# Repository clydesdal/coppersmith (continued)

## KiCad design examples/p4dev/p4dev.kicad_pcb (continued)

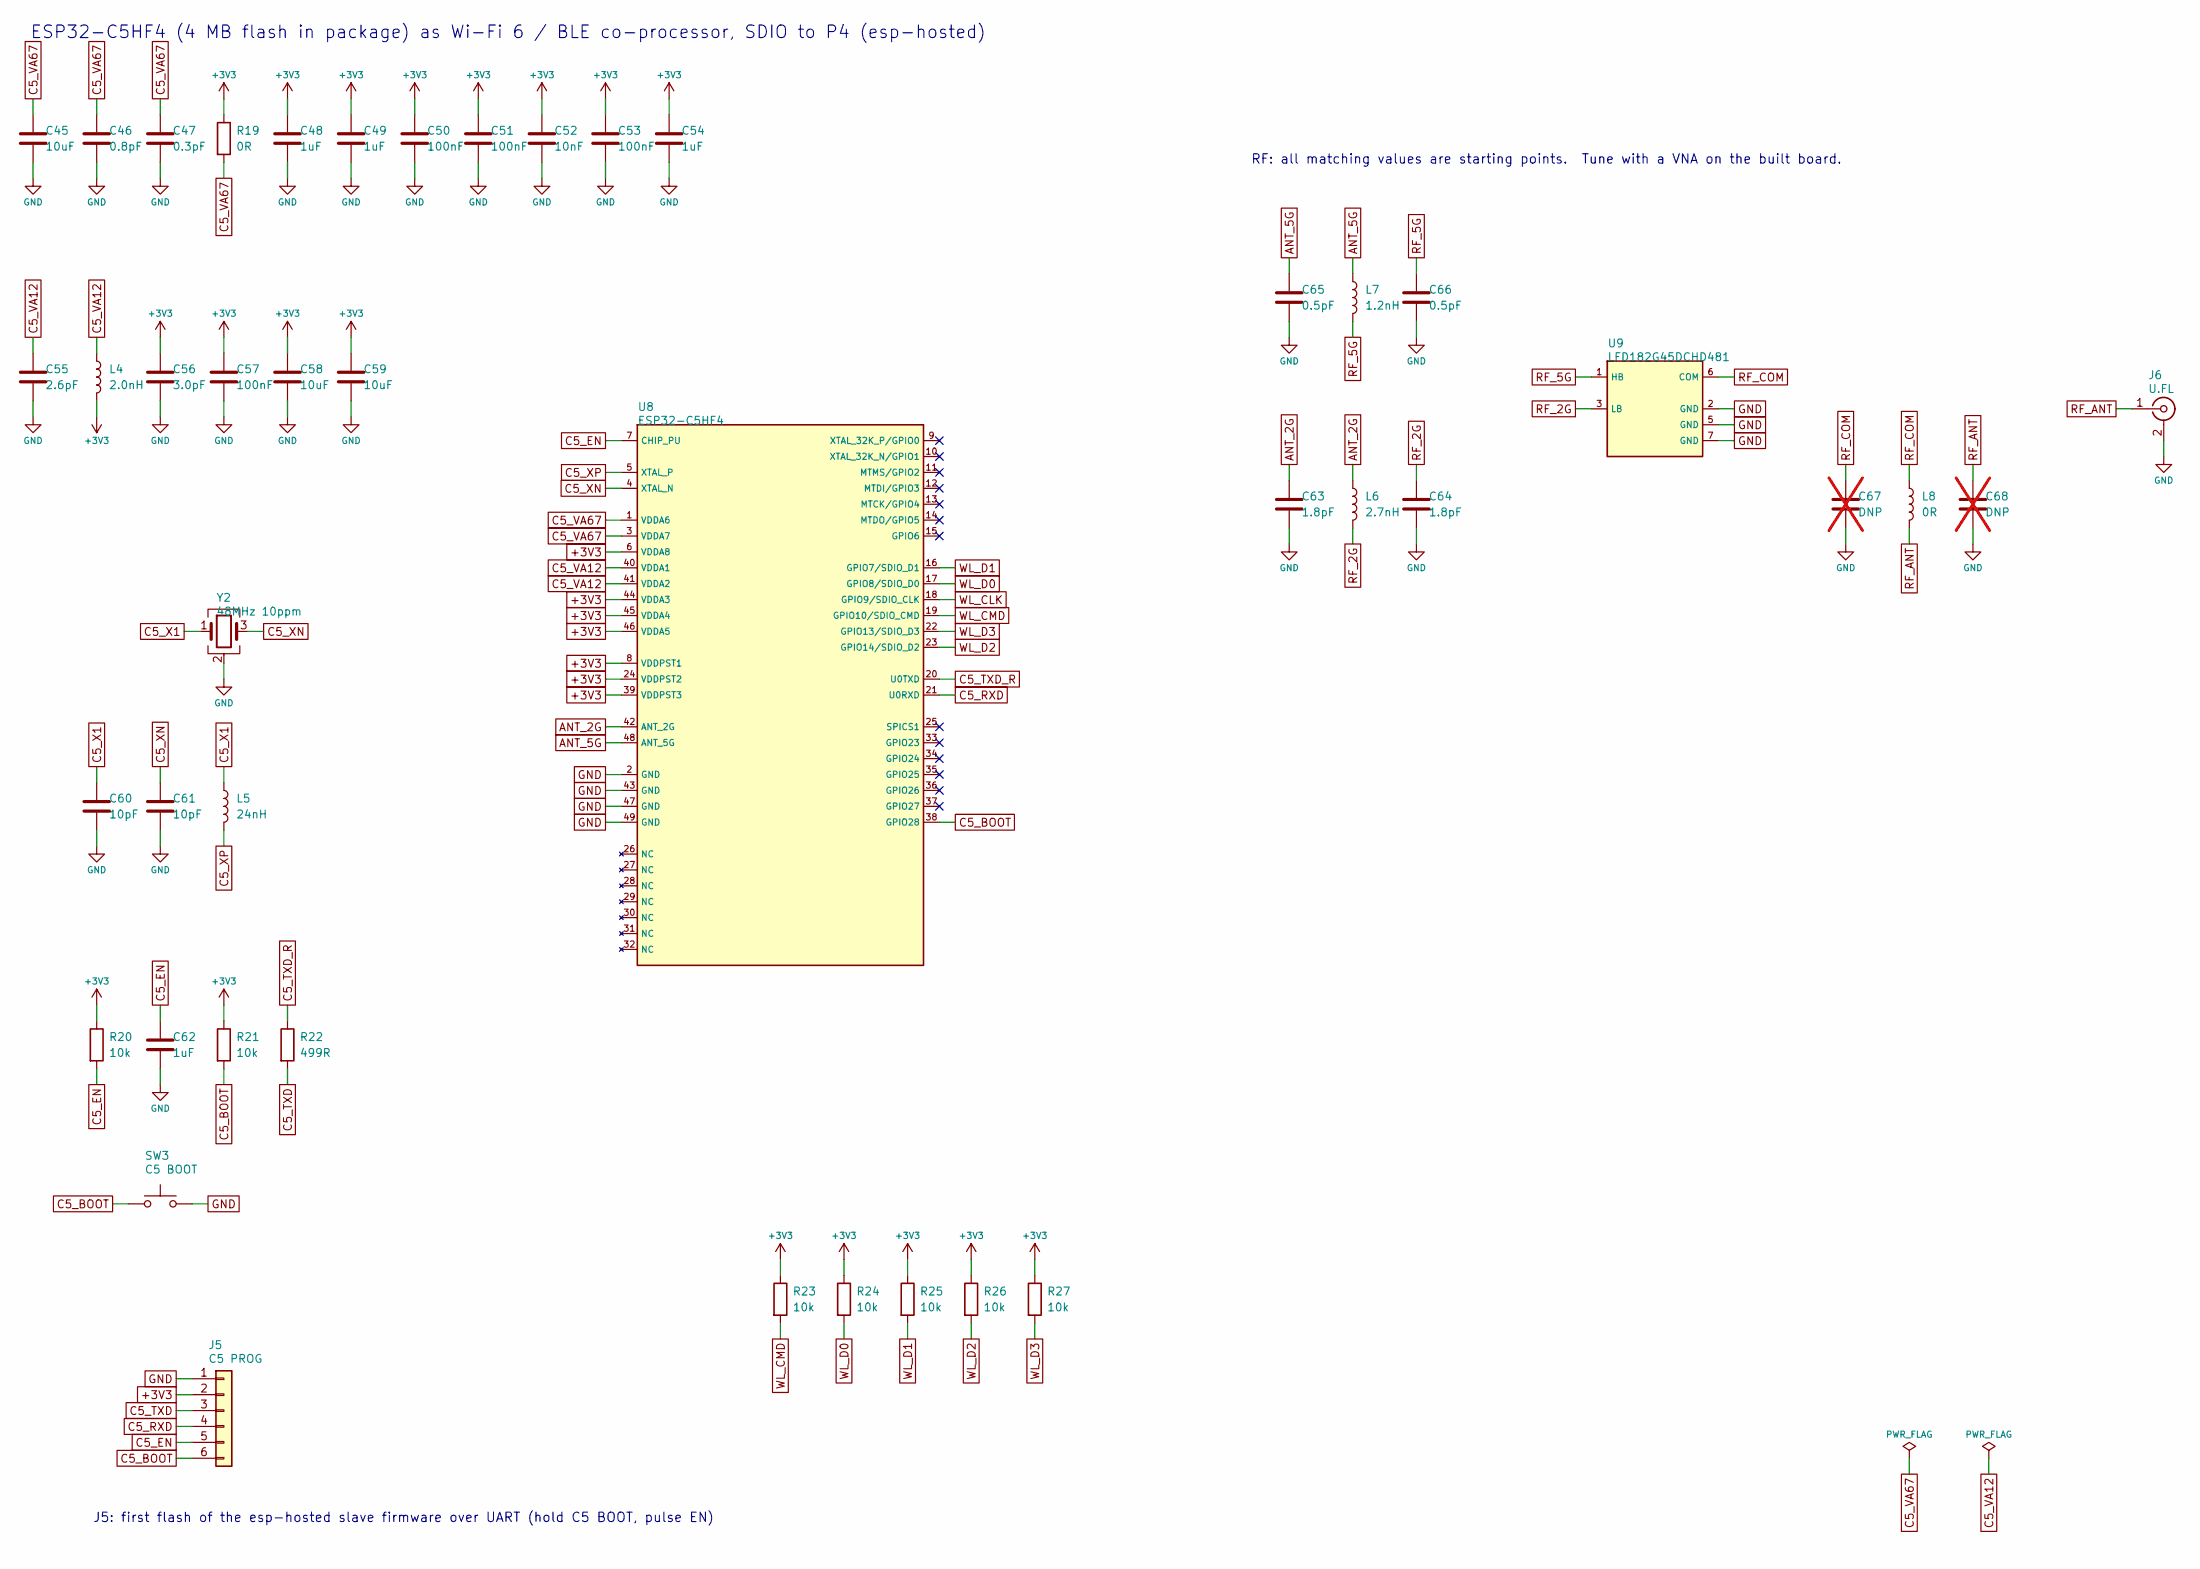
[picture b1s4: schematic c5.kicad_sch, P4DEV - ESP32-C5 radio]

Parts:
C45, C58, C59: 10uF; C_0603_1608Metric
C46: 0.8pF; C_0201_0603Metric
C47: 0.3pF; C_0201_0603Metric
C48, C49, C54, C62: 1uF; C_0402_1005Metric
C50, C51, C53, C57: 100nF; C_0402_1005Metric
C52: 10nF; C_0402_1005Metric
C55: 2.6pF; C_0201_0603Metric
C56: 3.0pF; C_0201_0603Metric
C60, C61: 10pF; C_0402_1005Metric
C63, C64: 1.8pF; C_0201_0603Metric
C65, C66: 0.5pF; C_0201_0603Metric
C67, C68: DNP; C_0201_0603Metric; not fitted
J5: C5 PROG; PinHeader_1x06_P2.54mm_Vertical; MPN Sullins PRPC006SAAN-RC
J6: U.FL; U.FL_Hirose_U.FL-R-SMT-1_Vertical; MPN Hirose U.FL-R-SMT-1(10)
L4: 2.0nH; L_0201_0603Metric
L5: 24nH; L_0402_1005Metric
L6: 2.7nH; L_0201_0603Metric
L7: 1.2nH; L_0201_0603Metric
L8: 0R; L_0201_0603Metric
R19: 0R; R_0402_1005Metric
R20, R21, R23, R24, R25, R26, R27: 10k; R_0402_1005Metric
R22: 499R; R_0402_1005Metric
SW3: C5 BOOT; SW_Push_1P1T_NO_CK_KMR2; MPN C&K KMR221GLFS
U8: ESP32-C5HF4; QFN-48-1EP_6x6mm_P0.4mm_EP4.66x4.66mm; MPN ESP32-C5HF4
U9: LFD182G45DCHD481; Murata_LFD18_Diplexer; MPN LFD182G45DCHD481
Y2: 48MHz 10ppm; Crystal_SMD_2016-4Pin_2.0x1.6mm; MPN 48 MHz, CL 8 pF, 2016

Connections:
+3V3: C48.1, C49.1, C50.1, C51.1, C52.1, C53.1, C54.1, C56.1, C57.1, C58.1, C59.1, J5.2, L4.2, R19.1, R20.1, R21.1, R23.1, R24.1, R25.1, R26.1, R27.1, U8.6 (VDDA8), U8.8 (VDDPST1), U8.24 (VDDPST2), U8.39 (VDDPST3), U8.44 (VDDA3), U8.45 (VDDA4), U8.46 (VDDA5); also elsewhere on the board
ANT_2G: C63.1, L6.1, U8.42 (ANT_2G)
ANT_5G: C65.1, L7.1, U8.48 (ANT_5G)
C5_BOOT: J5.6, R21.2, SW3.1, U8.38 (GPIO28)
C5_EN: C62.1, J5.5, R20.2, U8.7 (CHIP_PU); also elsewhere on the board
C5_RXD: J5.4, U8.21 (U0RXD)
C5_TXD: J5.3, R22.2
C5_TXD_R: R22.1, U8.20 (U0TXD)
C5_VA12: C55.1, L4.1, U8.40 (VDDA1), U8.41 (VDDA2)
C5_VA67: C45.1, C46.1, C47.1, R19.2, U8.1 (VDDA6), U8.3 (VDDA7)
C5_X1: C60.1, L5.1, Y2.1
C5_XN: C61.1, U8.4 (XTAL_N), Y2.3
C5_XP: L5.2, U8.5 (XTAL_P)
GND: C45.2, C46.2, C47.2, C48.2, C49.2, C50.2, C51.2, C52.2, C53.2, C54.2, C55.2, C56.2, C57.2, C58.2, C59.2, C60.2, C61.2, C62.2, C63.2, C64.2, C65.2, C66.2, C67.2, C68.2, J5.1, J6.2 (Ext), SW3.2, U8.2 (GND), U8.43 (GND), U8.47 (GND), U8.49 (GND), U9.2 (GND), U9.5 (GND), U9.7 (GND), Y2.2 (G), Y2.4 (G); also elsewhere on the board
RF_2G: C64.1, L6.2, U9.3 (LB)
RF_5G: C66.1, L7.2, U9.1 (HB)
RF_ANT: C68.1, J6.1 (In), L8.2
RF_COM: C67.1, L8.1, U9.6 (COM)
WL_CLK: U8.18 (GPIO9/SDIO_CLK); also elsewhere on the board
WL_CMD: R23.2, U8.19 (GPIO10/SDIO_CMD); also elsewhere on the board
WL_D0: R24.2, U8.17 (GPIO8/SDIO_D0); also elsewhere on the board
WL_D1: R25.2, U8.16 (GPIO7/SDIO_D1); also elsewhere on the board
WL_D2: R26.2, U8.23 (GPIO14/SDIO_D2); also elsewhere on the board
WL_D3: R27.2, U8.22 (GPIO13/SDIO_D3); also elsewhere on the board

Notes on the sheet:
ESP32-C5HF4 (4 MB flash in package) as Wi-Fi 6 / BLE co-processor, SDIO to P4 (esp-hosted)
RF: all matching values are starting points. Tune with a VNA on the built board.
J5: first flash of the esp-hosted slave firmware over UART (hold C5 BOOT, pulse EN)

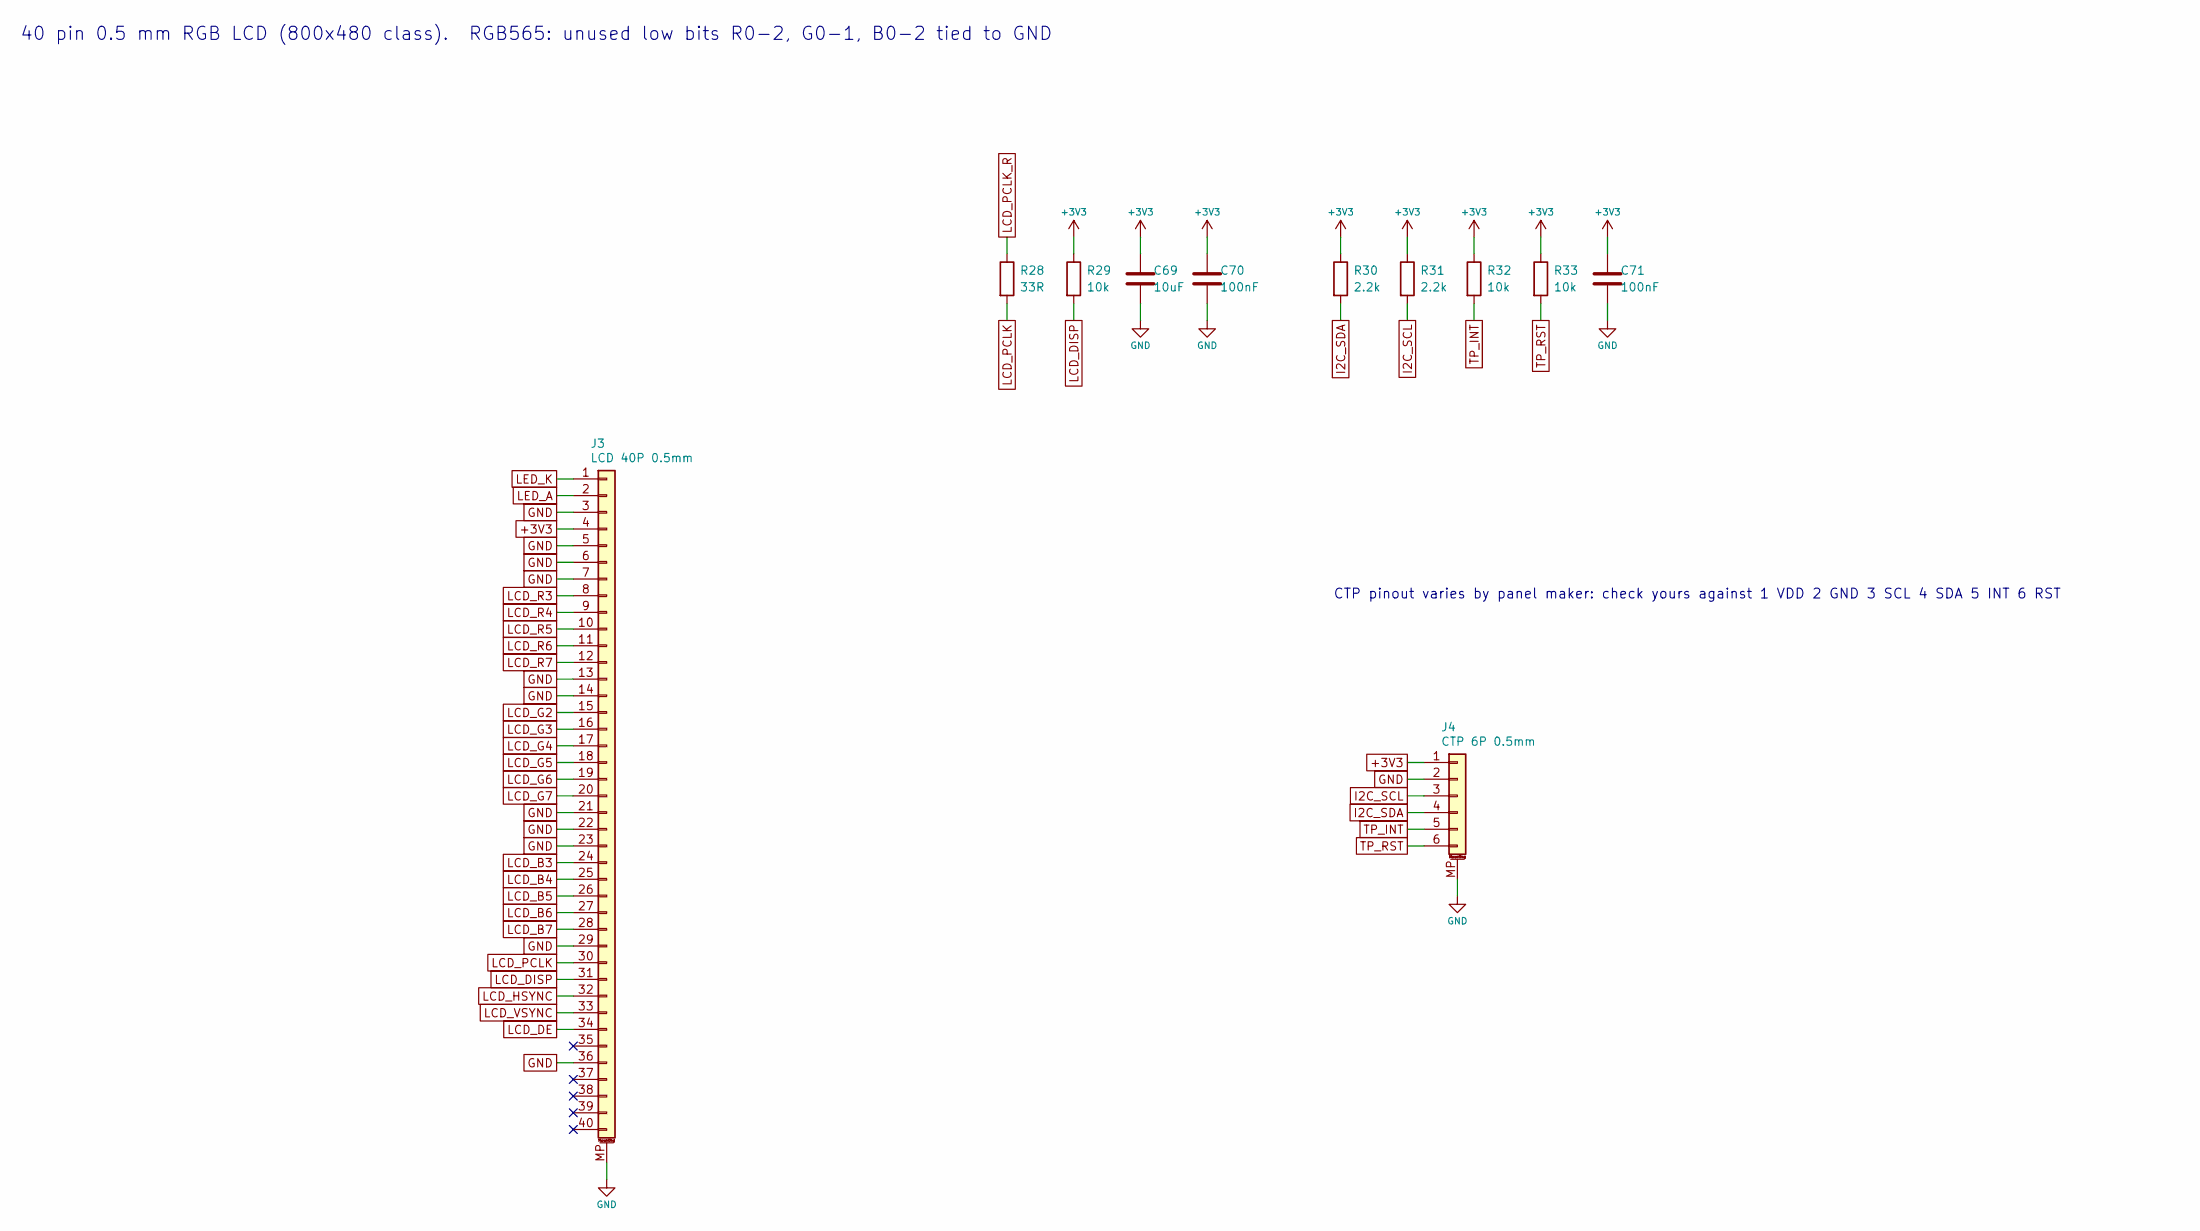
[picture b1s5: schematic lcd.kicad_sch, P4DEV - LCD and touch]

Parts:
C69: 10uF; C_0603_1608Metric
C70, C71: 100nF; C_0402_1005Metric
J3: LCD 40P 0.5mm; Hirose_FH12-40S-0.5SH_1x40-1MP_P0.50mm_Horizontal; MPN Hirose FH12-40S-0.5SH(55)
J4: CTP 6P 0.5mm; Hirose_FH12-6S-0.5SH_1x06-1MP_P0.50mm_Horizontal; MPN Hirose FH12-6S-0.5SH(55)
R28: 33R; R_0402_1005Metric
R29, R32, R33: 10k; R_0402_1005Metric
R30, R31: 2.2k; R_0402_1005Metric

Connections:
+3V3: C69.1, C70.1, C71.1, J3.4, J4.1, R29.1, R30.1, R31.1, R32.1, R33.1; also elsewhere on the board
GND: C69.2, C70.2, C71.2, J3.3, J3.5, J3.6, J3.7, J3.13, J3.14, J3.21, J3.22, J3.23, J3.29, J3.36, J3.MP (MountPin), J4.2, J4.MP (MountPin); also elsewhere on the board
I2C_SCL: J4.3, R31.2; also elsewhere on the board
I2C_SDA: J4.4, R30.2; also elsewhere on the board
LCD_B3: J3.24; also elsewhere on the board
LCD_B4: J3.25; also elsewhere on the board
LCD_B5: J3.26; also elsewhere on the board
LCD_B6: J3.27; also elsewhere on the board
LCD_B7: J3.28; also elsewhere on the board
LCD_DE: J3.34; also elsewhere on the board
LCD_DISP: J3.31, R29.2
LCD_G2: J3.15; also elsewhere on the board
LCD_G3: J3.16; also elsewhere on the board
LCD_G4: J3.17; also elsewhere on the board
LCD_G5: J3.18; also elsewhere on the board
LCD_G6: J3.19; also elsewhere on the board
LCD_G7: J3.20; also elsewhere on the board
LCD_HSYNC: J3.32; also elsewhere on the board
LCD_PCLK: J3.30, R28.2
LCD_PCLK_R: R28.1; also elsewhere on the board
LCD_R3: J3.8; also elsewhere on the board
LCD_R4: J3.9; also elsewhere on the board
LCD_R5: J3.10; also elsewhere on the board
LCD_R6: J3.11; also elsewhere on the board
LCD_R7: J3.12; also elsewhere on the board
LCD_VSYNC: J3.33; also elsewhere on the board
LED_A: J3.2; also elsewhere on the board
LED_K: J3.1; also elsewhere on the board
TP_INT: J4.5, R32.2; also elsewhere on the board
TP_RST: J4.6, R33.2; also elsewhere on the board

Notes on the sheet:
40 pin 0.5 mm RGB LCD (800x480 class). RGB565: unused low bits R0-2, G0-1, B0-2 tied to GND
CTP pinout varies by panel maker: check yours against 1 VDD 2 GND 3 SCL 4 SDA 5 INT 6 RST

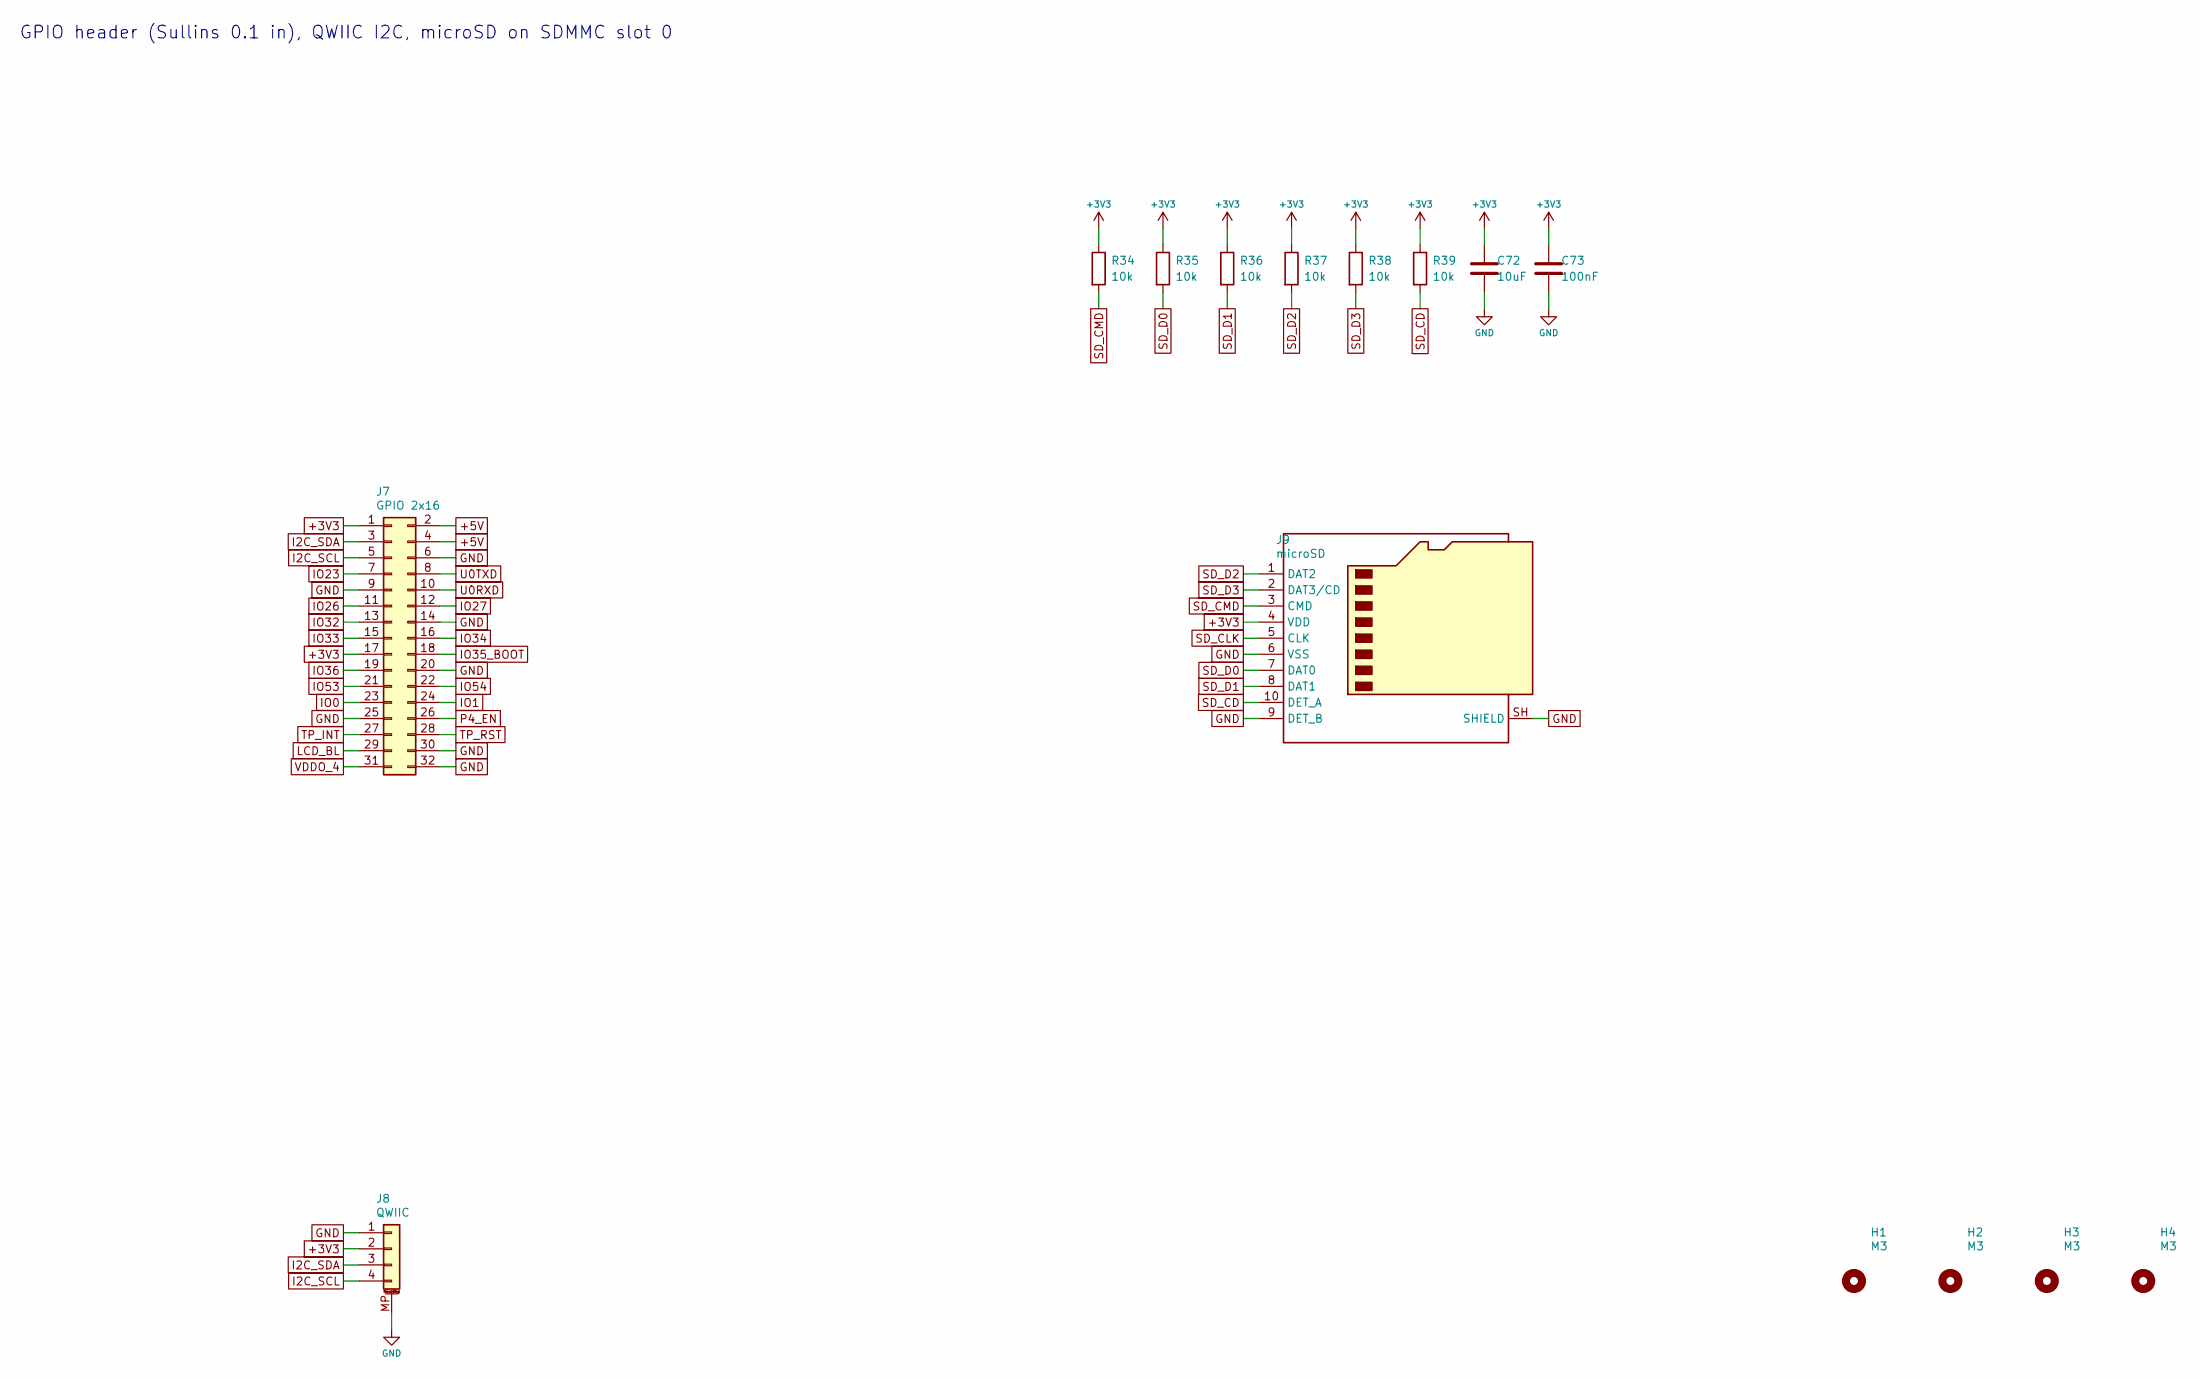
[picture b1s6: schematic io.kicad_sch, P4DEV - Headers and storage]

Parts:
C72: 10uF; C_0603_1608Metric
C73: 100nF; C_0402_1005Metric
H1, H2, H3, H4: M3; MountingHole_3.2mm_M3
J7: GPIO 2x16; PinHeader_2x16_P2.54mm_Vertical; MPN Sullins PRPC016DAAN-RC
J8: QWIIC; JST_SH_SM04B-SRSS-TB_1x04-1MP_P1.00mm_Horizontal; MPN JST SM04B-SRSS-TB
J9: microSD; microSD_HC_Hirose_DM3AT-SF-PEJM5; MPN Hirose DM3AT-SF-PEJM5
R34, R35, R36, R37, R38, R39: 10k; R_0402_1005Metric

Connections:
+3V3: C72.1, C73.1, J7.1, J7.17, J8.2, J9.4 (VDD), R34.1, R35.1, R36.1, R37.1, R38.1, R39.1; also elsewhere on the board
+5V: J7.2, J7.4; also elsewhere on the board
GND: C72.2, C73.2, J7.6, J7.9, J7.14, J7.20, J7.25, J7.30, J7.32, J8.1, J8.MP (MountPin), J9.6 (VSS), J9.9 (DET_B), J9.SH (SHIELD); also elsewhere on the board
I2C_SCL: J7.5, J8.4; also elsewhere on the board
I2C_SDA: J7.3, J8.3; also elsewhere on the board
IO0: J7.23; also elsewhere on the board
IO1: J7.24; also elsewhere on the board
IO23: J7.7; also elsewhere on the board
IO26: J7.11; also elsewhere on the board
IO27: J7.12; also elsewhere on the board
IO32: J7.13; also elsewhere on the board
IO33: J7.15; also elsewhere on the board
IO34: J7.16; also elsewhere on the board
IO35_BOOT: J7.18; also elsewhere on the board
IO36: J7.19; also elsewhere on the board
IO53: J7.21; also elsewhere on the board
IO54: J7.22; also elsewhere on the board
LCD_BL: J7.29; also elsewhere on the board
P4_EN: J7.26; also elsewhere on the board
SD_CD: J9.10 (DET_A), R39.2; also elsewhere on the board
SD_CLK: J9.5 (CLK); also elsewhere on the board
SD_CMD: J9.3 (CMD), R34.2; also elsewhere on the board
SD_D0: J9.7 (DAT0), R35.2; also elsewhere on the board
SD_D1: J9.8 (DAT1), R36.2; also elsewhere on the board
SD_D2: J9.1 (DAT2), R37.2; also elsewhere on the board
SD_D3: J9.2 (DAT3/CD), R38.2; also elsewhere on the board
TP_INT: J7.27; also elsewhere on the board
TP_RST: J7.28; also elsewhere on the board
U0RXD: J7.10; also elsewhere on the board
U0TXD: J7.8; also elsewhere on the board
VDDO_4: J7.31; also elsewhere on the board

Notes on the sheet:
GPIO header (Sullins 0.1 in), QWIIC I2C, microSD on SDMMC slot 0

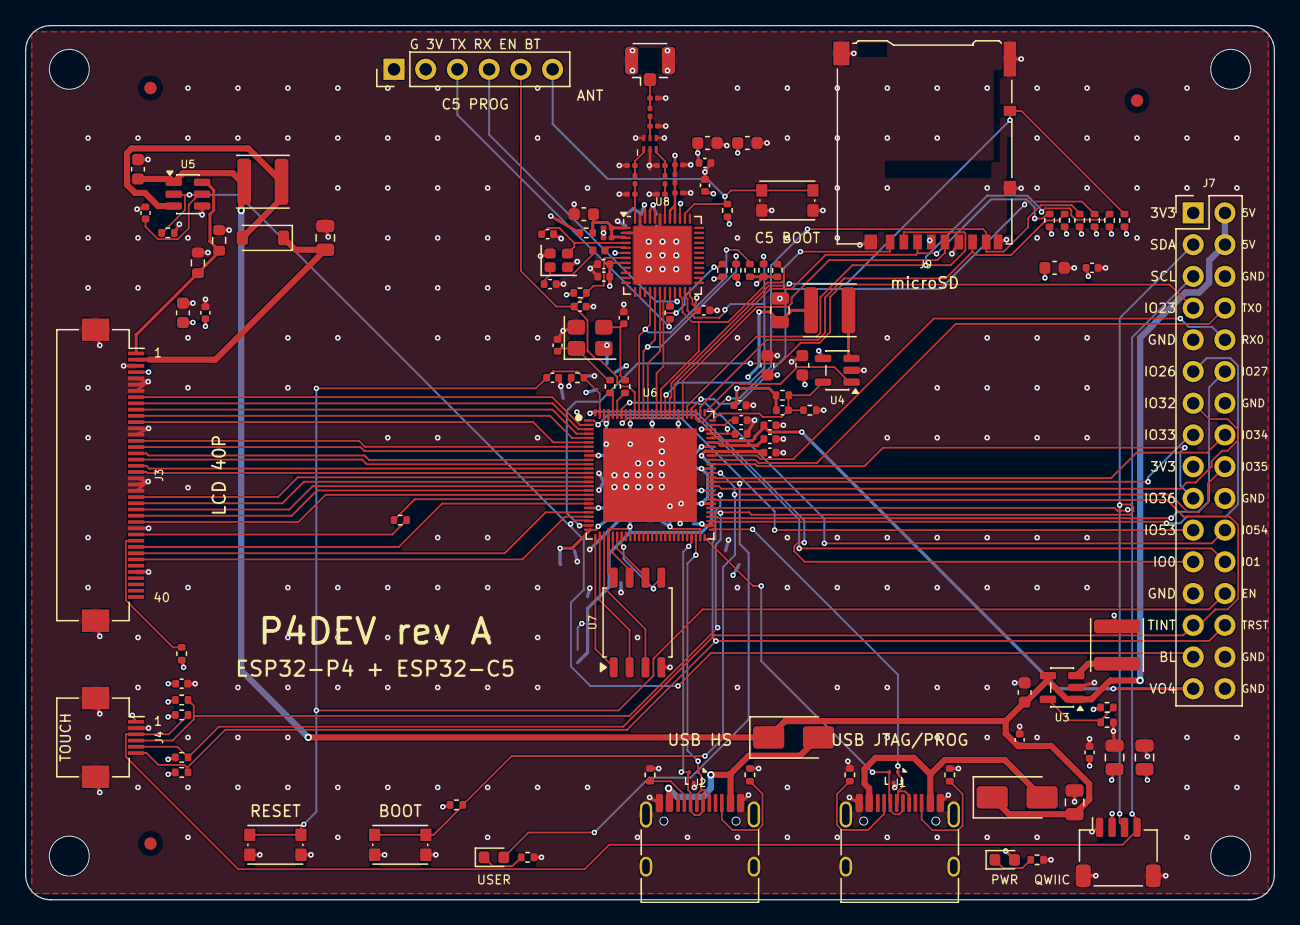
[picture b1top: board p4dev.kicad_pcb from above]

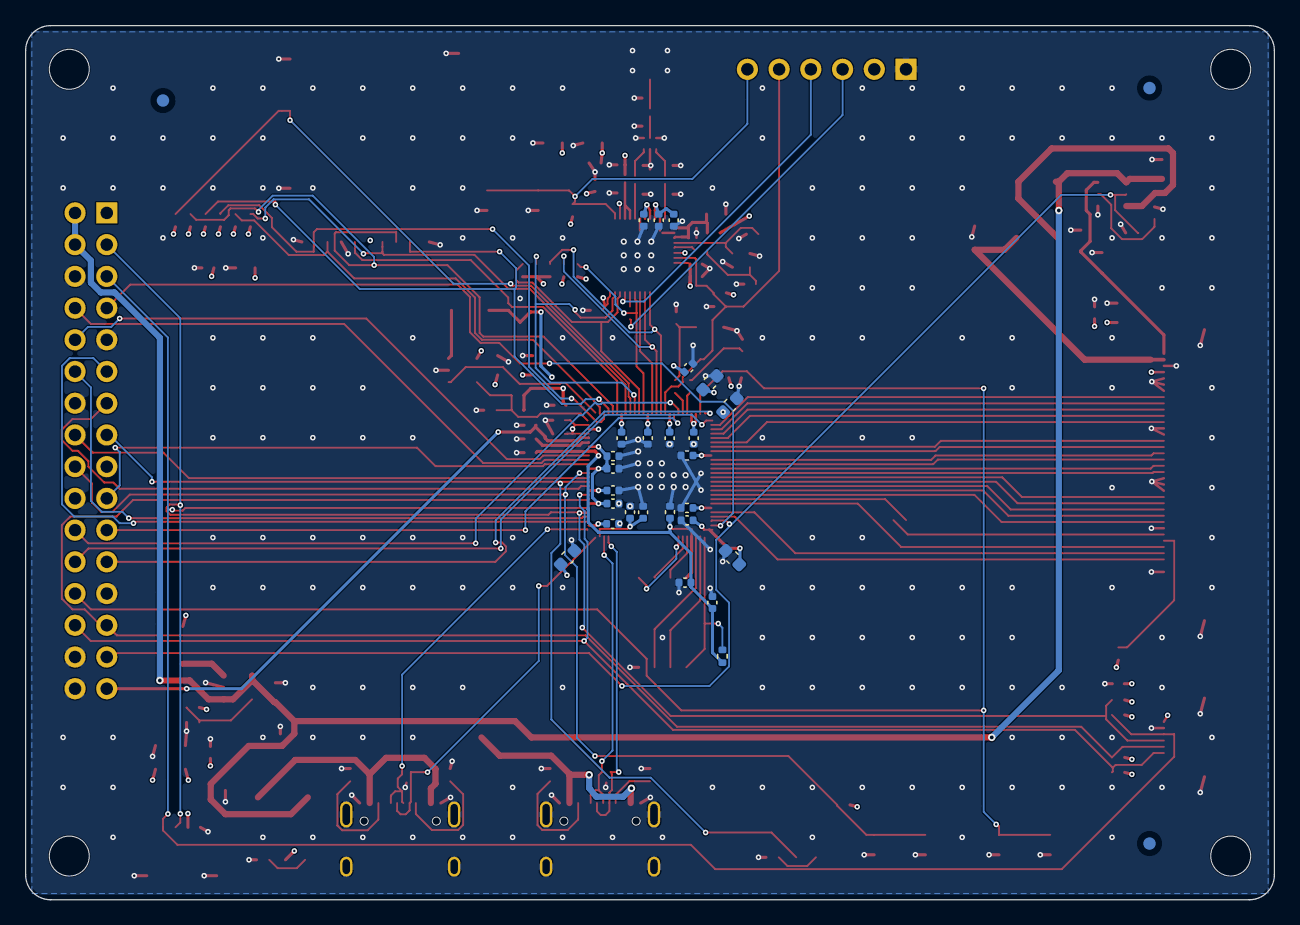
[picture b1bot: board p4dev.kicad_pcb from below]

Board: 4 copper layers, 100.0 x 70.0 mm, 158 parts (29 on the bottom side), 110 nets.

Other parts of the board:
FID1, FID2, FID3, FID4, FID5, FID6: Fiducial; Fiducial_1mm_Mask2mm
